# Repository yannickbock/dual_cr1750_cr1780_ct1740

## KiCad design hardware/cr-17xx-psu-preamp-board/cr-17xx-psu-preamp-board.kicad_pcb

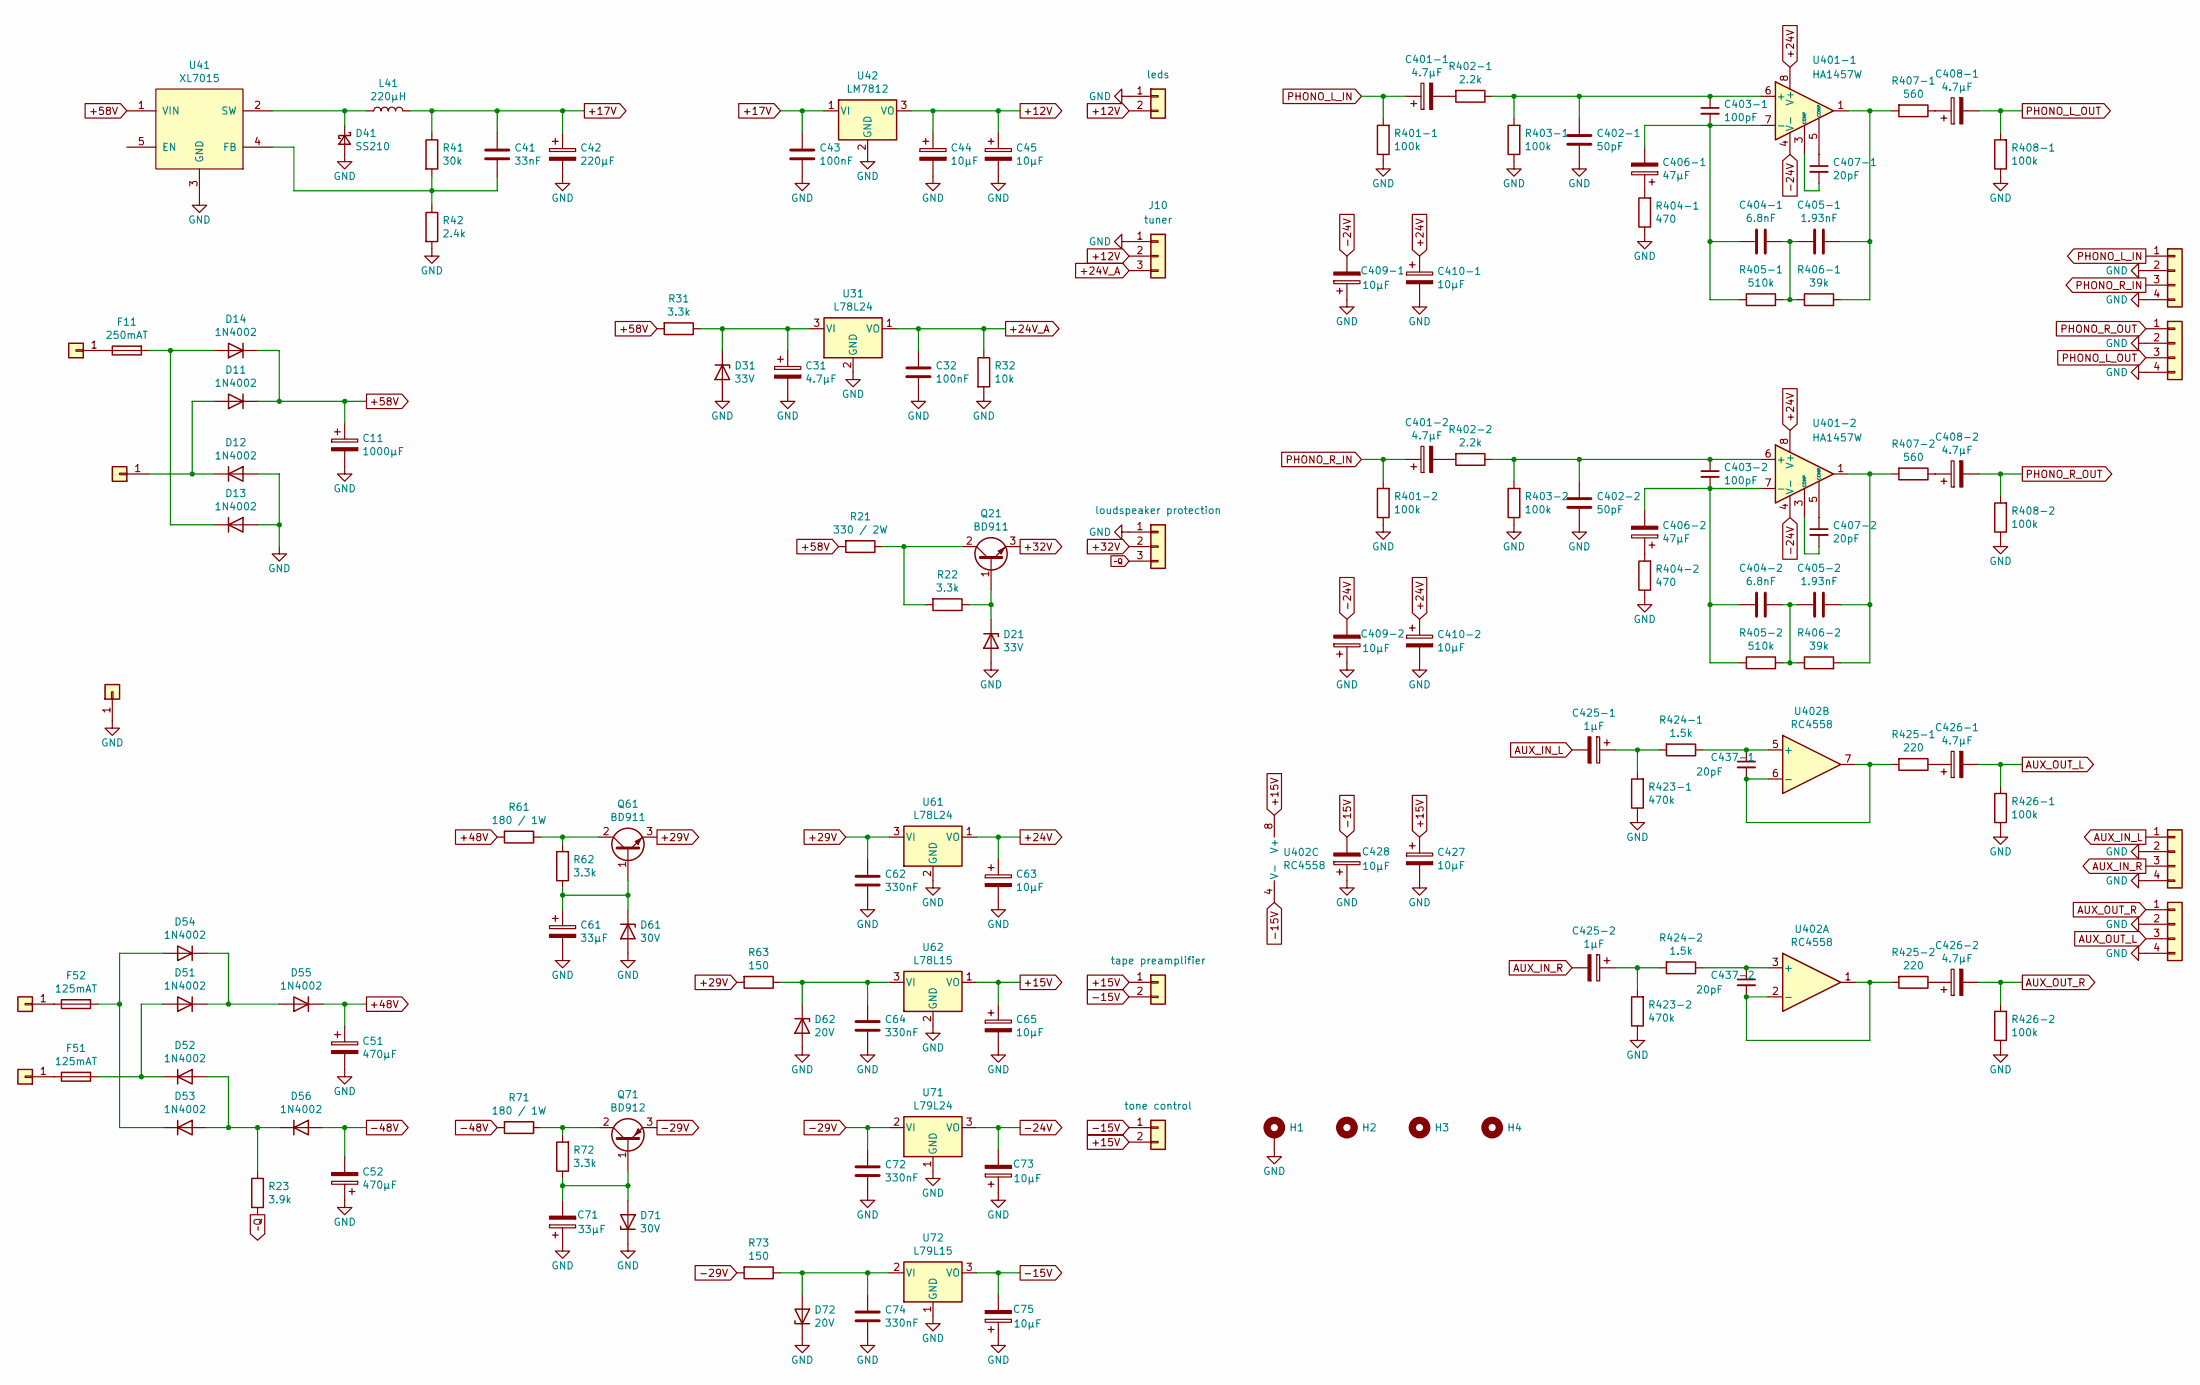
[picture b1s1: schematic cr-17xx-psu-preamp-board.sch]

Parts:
C11: 1000µF; CP_Radial_D17.0mm_P7.50mm
C31, C401-1, C401-2, C408-1, C408-2, C426-1, C426-2: 4.7µF; CP_Radial_D5.0mm_P2.00mm
C32, C43: 100nF; C_Disc_D4.3mm_W1.9mm_P5.00mm
C41: 33nF; C_0805_HandSoldering; LCSC C1739
C42: 220µF; CP_Radial_D10.0mm_P5.00mm
C44, C45, C63, C65, C73, C75, C409-1, C409-2, C410-1, C410-2, C427, C428: 10µF; CP_Radial_D5.0mm_P2.00mm
C51, C52: 470µF; CP_Radial_D12.5mm_P5.00mm
C61, C71: 33µF; CP_Radial_D5.0mm_P2.00mm
C62, C64, C72, C74: 330nF; C_Disc_D4.3mm_W1.9mm_P5.00mm
C402-1, C402-2: 50pF; C_Disc_D4.3mm_W1.9mm_P5.00mm
C403-1, C403-2: 100pF; C_Disc_D4.3mm_W1.9mm_P5.00mm
C404-1, C404-2: 6.8nF; C_Disc_D4.3mm_W1.9mm_P5.00mm
C405-1, C405-2: 1.93nF; C_Disc_D4.3mm_W1.9mm_P5.00mm
C406-1, C406-2: 47µF; CP_Radial_D5.0mm_P2.00mm
C407-1, C407-2, C437-1, C437-2: 20pF; C_Disc_D4.3mm_W1.9mm_P5.00mm
C425-1, C425-2: 1µF; CP_Radial_D5.0mm_P2.00mm
D11, D12, D13, D14, D51, D52, D53, D54, D55, D56: 1N4002; D_DO-41_SOD81_P10.16mm_Horizontal
D21, D31: 33V; D_DO-35_SOD27_P10.16mm_Horizontal
D41: SS210; D_SMA; LCSC C14996
D61, D71: 30V; D_DO-35_SOD27_P10.16mm_Horizontal
D62, D72: 20V; D_DO-35_SOD27_P7.62mm_Horizontal
F11: 250mAT; Fuseholder5x20_horiz_open_inline_Type-I
F51, F52: 125mAT; Fuseholder5x20_horiz_open_inline_Type-I
H1: MountingHole_Pad; MountingHole_4mm_Pad
H2, H3, H4: MountingHole; MountingHole_4mm
J1: leds; JST_XH_B02B-XH-A_02x2.50mm_Straight
J2, J3, J4, J5, J6: Conn_01x01; SolderWirePad_single_1mmDrill
J7: tape preamplifier; JST_XH_B02B-XH-A_02x2.50mm_Straight
J8: tone control; JST_XH_B02B-XH-A_02x2.50mm_Straight
J9: loudspeaker protection; JST_XH_B03B-XH-A_03x2.50mm_Straight
J10: tuner; JST_XH_B03B-XH-A_03x2.50mm_Straight
J11, J12, J13, J14: Conn_01x04; JST_XH_B04B-XH-A_04x2.50mm_Straight
L41: 220µH; L-Sunlord-SWPA6045SxxxMT; LCSC C91047
Q21, Q61: BD911; TO-220-3_Vertical
Q71: BD912; TO-220-3_Vertical
R21: 330 / 2W; R_Axial_DIN0614_L14.3mm_D5.7mm_P20.32mm_Horizontal
R22, R31, R62, R72: 3.3k; R_Axial_DIN0207_L6.3mm_D2.5mm_P10.16mm_Horizontal
R23: 3.9k; R_Axial_DIN0207_L6.3mm_D2.5mm_P10.16mm_Horizontal
R32: 10k; R_Axial_DIN0207_L6.3mm_D2.5mm_P10.16mm_Horizontal
R41: 30k; R_0805_HandSoldering; LCSC C17621
R42: 2.4k; R_0805_HandSoldering; LCSC C17526
R61, R71: 180 / 1W; R_Axial_DIN0414_L11.9mm_D4.5mm_P15.24mm_Horizontal
R63, R73: 150; R_Axial_DIN0414_L11.9mm_D4.5mm_P15.24mm_Horizontal
R401-1, R401-2, R403-1, R403-2, R408-1, R408-2, R426-1, R426-2: 100k; R_Axial_DIN0207_L6.3mm_D2.5mm_P10.16mm_Horizontal
R402-1, R402-2: 2.2k; R_Axial_DIN0207_L6.3mm_D2.5mm_P10.16mm_Horizontal
R404-1, R404-2: 470; R_Axial_DIN0207_L6.3mm_D2.5mm_P10.16mm_Horizontal
R405-1, R405-2: 510k; R_Axial_DIN0207_L6.3mm_D2.5mm_P10.16mm_Horizontal
R406-1, R406-2: 39k; R_Axial_DIN0207_L6.3mm_D2.5mm_P10.16mm_Horizontal
R407-1, R407-2: 560; R_Axial_DIN0207_L6.3mm_D2.5mm_P10.16mm_Horizontal
R423-1, R423-2: 470k; R_Axial_DIN0207_L6.3mm_D2.5mm_P10.16mm_Horizontal
R424-1, R424-2: 1.5k; R_Axial_DIN0207_L6.3mm_D2.5mm_P10.16mm_Horizontal
R425-1, R425-2: 220; R_Axial_DIN0207_L6.3mm_D2.5mm_P10.16mm_Horizontal
U31, U61: L78L24; TO-92_Inline_Wide
U41: XL7015; TO-252-5_TabPin3; LCSC C73013
U42: LM7812; TO-220-3_Vertical
U62: L78L15; TO-92_Inline_Wide
U71: L79L24; TO-92_Inline_Wide
U72: L79L15; TO-92_Inline_Wide
U401-1, U401-2: HA1457W; SIP8_NO_PIN_7
U402: RC4558; DIP-8_W7.62mm_LongPads

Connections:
+12V: C44.1, C45.1, J1.2, J10.2, U42.3 (VO)
+15V: C65.1, C427.1, J7.1, J8.2, U62.1 (VO), U402.8 (V+)
+17V: C41.1, C42.1, C43.1, L41.2, R41.1, U42.1 (VI)
+24V: C63.1, C410-1.1, C410-2.1, U61.1 (VO), U401-1.8 (V+), U401-2.8 (V+)
+24V_A: C32.1, J10.3, R32.1, U31.1 (VO)
+29V: C62.1, Q61.3 (E), R63.2, U61.3 (VI)
+32V: J9.2, Q21.3 (E)
+48V: C51.1, D55.1 (K), R61.2
+58V: C11.1, D11.1 (K), D14.1 (K), R21.2, R31.2, U41.1 (VIN)
-15V: C75.2, C428.2, J7.2, J8.1, U72.3 (VO), U402.4 (V-)
-24V: C73.2, C409-1.2, C409-2.2, U71.3 (VO), U401-1.4 (V-), U401-2.4 (V-)
-29V: C72.1, Q71.3 (E), R73.2, U71.2 (VI)
-48V: C52.2, D56.2 (A), R71.2
AUX_IN_L: C425-1.2, J11.1
AUX_IN_R: C425-2.2, J11.3
AUX_OUT_L: C426-1.2, J13.3, R426-1.2
AUX_OUT_R: C426-2.2, J13.1, R426-2.2
GND: C11.2, C31.2, C32.2, C42.2, C43.2, C44.2, C45.2, C51.2, C52.1, C61.2, C62.2, C63.2, C64.2, C65.2, C71.1, C72.2, C73.1, C74.2, C75.1, C402-1.2, C402-2.2, C409-1.1, C409-2.1, C410-1.2, C410-2.2, C427.2, C428.1, D12.2 (A), D13.2 (A), D21.2 (A), D31.2 (A), D41.2 (A), D61.2 (A), D62.2 (A), D71.1 (K), D72.1 (K), H1.1, J1.1, J4.1, J9.1, J10.1, J11.2, J11.4, J12.2, J12.4, J13.2, J13.4, J14.2, J14.4, R32.2, R42.2, R401-1.1, R401-2.1, R403-1.1, R403-2.1, R404-1.1, R404-2.1, R408-1.1, R408-2.1, R423-1.1, R423-2.1, R426-1.1, R426-2.1, U31.2 (GND), U41.3 (GND), U42.2 (GND), U61.2 (GND), U62.2 (GND), U71.1 (GND), U72.1 (GND)
unnamed: C31.1, D31.1 (K), R31.1, U31.3 (VI)
unnamed: C41.2, R41.2, R42.1, U41.4 (FB)
unnamed: C61.1, D61.1 (K), Q61.1 (B), R62.1
unnamed: C64.1, D62.1 (K), R63.1, U62.3 (VI)
unnamed: C71.2, D71.2 (A), Q71.1 (B), R72.1
unnamed: C74.1, D72.2 (A), R73.1, U72.2 (VI)
unnamed: C401-1.2, R402-1.2
unnamed: C401-2.2, R402-2.2
unnamed: C402-1.1, C403-1.1, R402-1.1, R403-1.2, U401-1.6 (+)
unnamed: C402-2.1, C403-2.1, R402-2.1, R403-2.2, U401-2.6 (+)
unnamed: C403-1.2, C404-1.2, C406-1.2, R405-1.1, U401-1.7 (-)
unnamed: C403-2.2, C404-2.2, C406-2.2, R405-2.1, U401-2.7 (-)
unnamed: C404-1.1, C405-1.2, R405-1.2, R406-1.1
unnamed: C404-2.1, C405-2.2, R405-2.2, R406-2.1
unnamed: C405-1.1, R406-1.2, R407-1.2, U401-1.1
unnamed: C405-2.1, R406-2.2, R407-2.2, U401-2.1
unnamed: C406-1.1, R404-1.2
unnamed: C406-2.1, R404-2.2
unnamed: C407-1.1, U401-1.5 (COMP)
unnamed: C407-1.2, U401-1.3 (COMP)
unnamed: C407-2.1, U401-2.5 (COMP)
unnamed: C407-2.2, U401-2.3 (COMP)
unnamed: C408-1.1, R407-1.1
unnamed: C408-2.1, R407-2.1
unnamed: C425-1.1, R423-1.2, R424-1.2
unnamed: C425-2.1, R423-2.2, R424-2.2
unnamed: C426-1.1, R425-1.1
unnamed: C426-2.1, R425-2.1
unnamed: C437-1.1, R424-1.1, U402.5 (+)
unnamed: C437-1.2, R425-1.2, U402.6 (-), U402.7
unnamed: C437-2.1, R424-2.1, U402.3 (+)
unnamed: C437-2.2, R425-2.2, U402.1, U402.2 (-)
unnamed: D11.2 (A), D12.1 (K), J5.1
unnamed: D13.1 (K), D14.2 (A), F11.2
unnamed: D21.1 (K), Q21.1 (B), R22.1
unnamed: D41.1 (K), L41.1, U41.2 (SW)
unnamed: D51.1 (K), D54.1 (K), D55.2 (A)
unnamed: D51.2 (A), D52.1 (K), F51.2
unnamed: D52.2 (A), D53.2 (A), D56.1 (K), R23.1
unnamed: D53.1 (K), D54.2 (A), F52.2
unnamed: F11.1, J6.1
unnamed: F51.1, J2.1
unnamed: F52.1, J3.1
unnamed: Q21.2 (C), R21.1, R22.2
unnamed: Q61.2 (C), R61.1, R62.2
unnamed: Q71.2 (C), R71.1, R72.2
PHONO_L_IN: C401-1.1, J12.1, R401-1.2
PHONO_L_OUT: C408-1.2, J14.3, R408-1.2
PHONO_R_IN: C401-2.1, J12.3, R401-2.2
PHONO_R_OUT: C408-2.2, J14.1, R408-2.2
~~Q: J9.3, R23.2

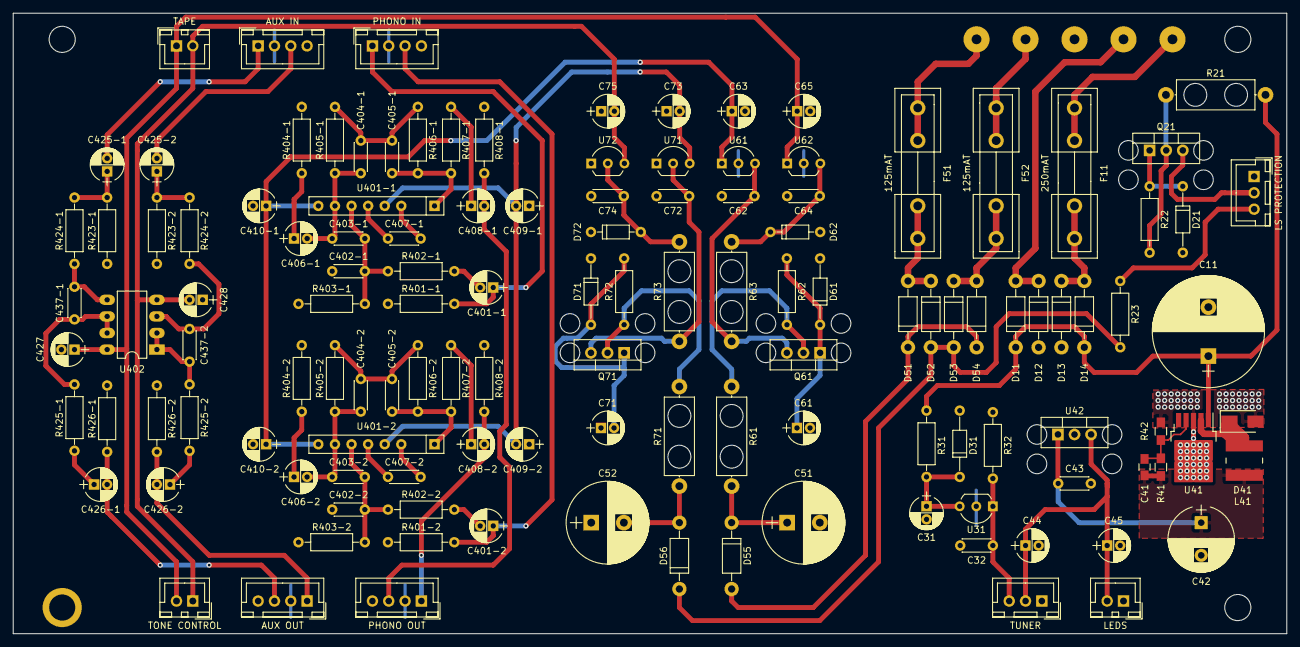
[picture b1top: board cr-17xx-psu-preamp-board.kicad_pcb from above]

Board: 2 copper layers, 195.0 x 95.0 mm, 137 parts (0 on the bottom side), 69 nets.

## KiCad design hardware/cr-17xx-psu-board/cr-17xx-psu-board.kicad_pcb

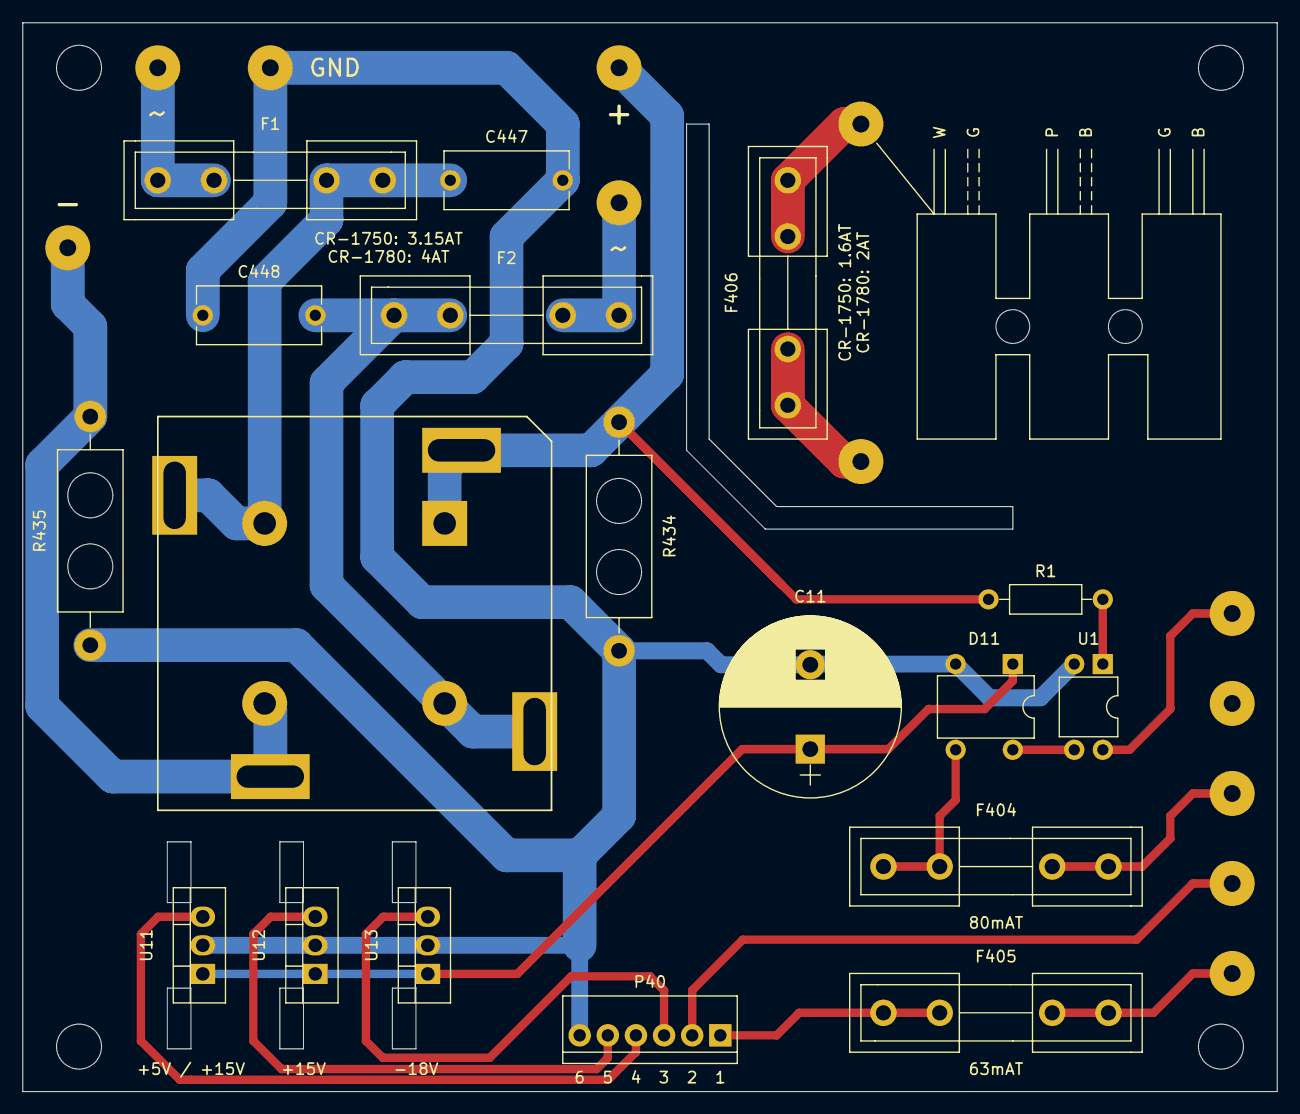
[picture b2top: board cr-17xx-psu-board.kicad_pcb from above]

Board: 2 copper layers, 111.5 x 95.0 mm, 36 parts (0 on the bottom side), 21 nets.

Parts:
C11: 1000µF; CP_Radial_D16.0mm_P7.50mm
C447, C448: 330nF; C_Rect_L11.0mm_W5.1mm_P10.00mm_MKT
D1: VS-KBPC804; Diode_Bridge
D11: B380C800DM; Diode_Bridge_DIP-4_W7.62mm_P5.08mm
F1, F2: 2.5AT / 3.15AT; Fuseholder5x20_horiz_open_inline_Type-I
F404: T100mA; Fuseholder5x20_horiz_open_inline_Type-I
F405: T63mA; Fuseholder5x20_horiz_open_inline_Type-I
F406: T1.6A / T2A; Fuseholder5x20_horiz_open_inline_Type-I
H1, H2, H3, H4: MountingHole; MountingHole_4mm
H5, H6: MountingHole; MountingHole_3mm
J1, J2, J3, J4, J5, J6, J7, J8, J9, J10, J11, J12: Conn_01x01; SolderWirePad_single_1-5mmDrill
P40: Conn_01x06
R1: 10k; R_Axial_DIN0207_L6.3mm_D2.5mm_P10.16mm_Horizontal
R434, R435: 4.7k; R_Axial_DIN0614_L14.3mm_D5.7mm_P20.32mm_Horizontal
U1: AQY282EH; DIP-4_W7.62mm
U11, U12: LM7815_TO220; TO-220-3_Vertical
U13: Conn_01x03; TO-220-3_Vertical

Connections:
+5V|+15V: P40.4, U11.3
+15V: P40.5, U12.3
+35V: C11.1, D11.1, U11.1, U12.1, U13.1
+A: D1.3, J9.1, R1.2, R434.1
-18V: P40.3, U13.3
-B: D1.1, J12.1, R435.1
GND: C11.2, C447.2, C448.2, D11.2, J8.1, P40.6, R434.2, R435.2, U1.2, U11.2, U12.2, U13.2
unnamed: C447.1, D1.4, F1.1
unnamed: C448.1, D1.2, F2.1
unnamed: F1.2, J10.1
unnamed: F2.2, J11.1
unnamed: F404.2, J3.1
unnamed: F405.2, J5.1
unnamed: F406.1, J7.1
unnamed: F406.2, J6.1
unnamed: J1.1, U1.4
unnamed: R1.1, U1.1
~~3.3V-L: F405.1, P40.1
~~3.3V-N: J4.1, P40.2
~~25V-L: D11.3, F404.1
~~25V-N: D11.4, U1.3

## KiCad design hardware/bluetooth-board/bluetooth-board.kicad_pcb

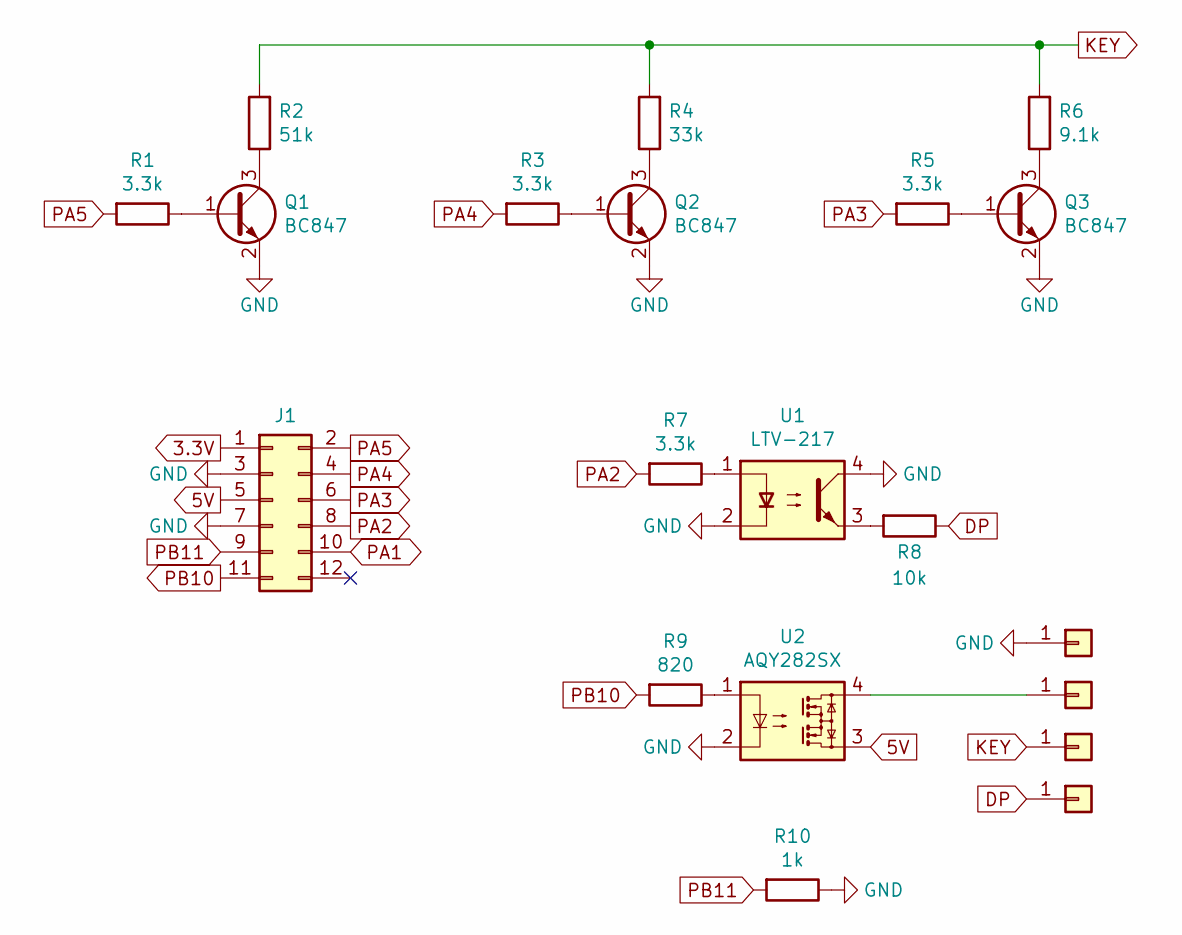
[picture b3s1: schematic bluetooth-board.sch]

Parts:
J1: Conn_02x06_Odd_Even; Socket_Strip_Straight_2x06_Pitch2.54mm
J2, J3, J4, J5: Conn_01x01; SolderWirePad_single_1mmDrill
Q1, Q2, Q3: BC847; SOT-23; LCSC C2145
R1, R3, R5, R7: 3.3k; R_0805; LCSC C26010
R2: 51k; R_0805; LCSC C17737
R4: 33k; R_0805; LCSC C17633
R6: 9.1k; R_0805; LCSC C17855
R8: 10k; R_0805; LCSC C17414
R9: 820; R_0805; LCSC C17837
R10: 1k; R_0805; LCSC C17513
U1: LTV-217; SOP-4_4.4x2.8mm_Pitch1.27mm; LCSC C691224
U2: AQY282SX; SOP-4_3.8x4.1mm_Pitch2.54mm; LCSC C250827

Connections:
3.3V: J1.1
5V: J1.5, U2.3
DP: J5.1, R8.1
GND: J1.3, J1.7, J2.1, Q1.2 (E), Q2.2 (E), Q3.2 (E), R10.1, U1.2, U1.4, U2.2
KEY: J4.1, R2.2, R4.2, R6.2
unnamed: J3.1, U2.4
unnamed: Q1.1 (B), R1.1
unnamed: Q1.3 (C), R2.1
unnamed: Q2.1 (B), R3.1
unnamed: Q2.3 (C), R4.1
unnamed: Q3.1 (B), R5.1
unnamed: Q3.3 (C), R6.1
unnamed: R7.1, U1.1
unnamed: R8.2, U1.3
unnamed: R9.1, U2.1
PA1: J1.10
PA2: J1.8, R7.2
PA3: J1.6, R5.2
PA4: J1.4, R3.2
PA5: J1.2, R1.2
PB10: J1.11, R9.2
PB11: J1.9, R10.2

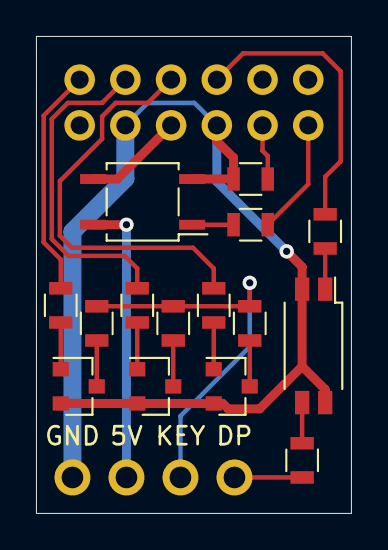
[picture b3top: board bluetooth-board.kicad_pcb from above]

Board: 2 copper layers, 17.5 x 26.5 mm, 20 parts (1 on the bottom side), 20 nets.

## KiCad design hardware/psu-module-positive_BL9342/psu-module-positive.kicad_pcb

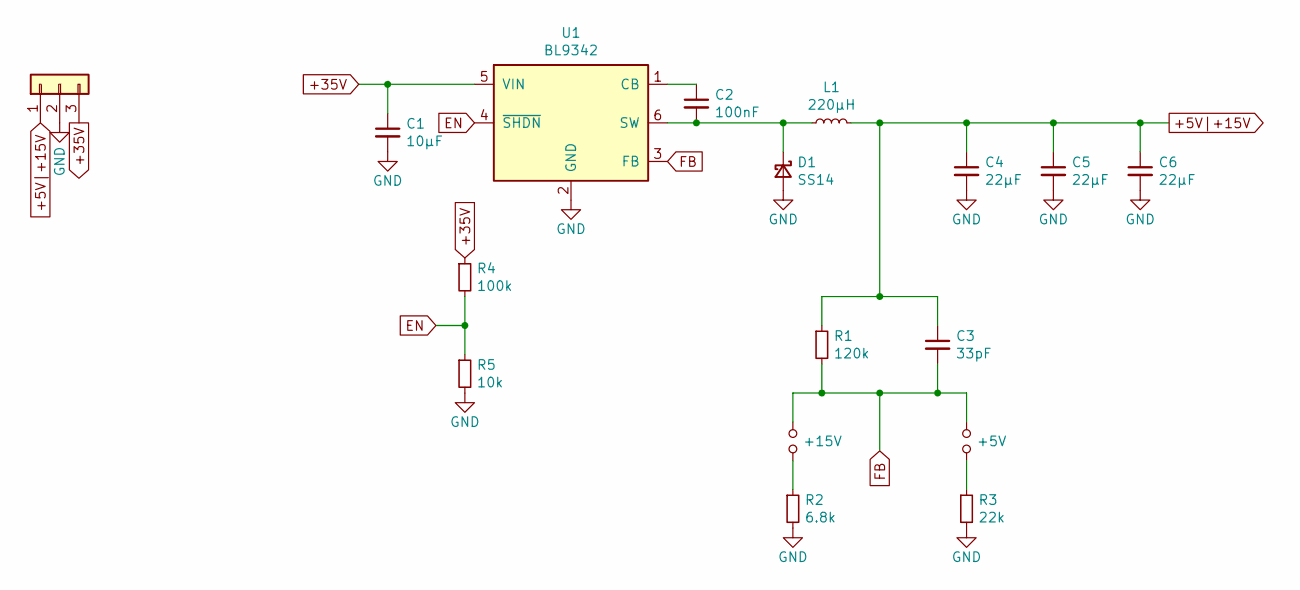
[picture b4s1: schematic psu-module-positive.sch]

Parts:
C1: 10µF; C_1206; LCSC C13585
C2: 100nF; C_0805; LCSC C49678
C3: 33pF; C_0805; LCSC C1814
C4, C5, C6: 22µF; C_0805; LCSC C45783
D1: SS14; D_SMA; LCSC C2480
J5: Conn_01x03; Pin_Header_Angled_1x03_Pitch2.54mm
JP1: +15V; WireConnection_0.80mmDrill_ThinPad
JP2: +5V; WireConnection_0.80mmDrill_ThinPad
L1: 220µH; L_Wuerth_WE-PD2-Typ-MS; LCSC C91047
R1: 120k; R_0805; LCSC C17436
R2: 6.8k; R_0805; LCSC C17772
R3: 22k; R_0805; LCSC C17560
R4: 100k; R_0805; LCSC C17407
R5: 10k; R_0805; LCSC C17414
U1: BL9342; SOT-23-6_Handsoldering; LCSC C93176

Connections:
+5V|+15V: C3.1, C4.1, C5.1, C6.1, J5.1, L1.2, R1.1
+35V: C1.1, J5.3, R4.1, U1.5 (VIN)
EN: R4.2, R5.1, U1.4 (~SHDN)
FB: C3.2, JP1.1, JP2.1, R1.2, U1.3 (FB)
GND: C1.2, C4.2, C5.2, C6.2, D1.2 (A), J5.2, R2.2, R3.2, R5.2, U1.2 (GND)
unnamed: C2.1, U1.1 (CB)
unnamed: C2.2, D1.1 (K), L1.1, U1.6 (SW)
unnamed: JP1.2, R2.1
unnamed: JP2.2, R3.1

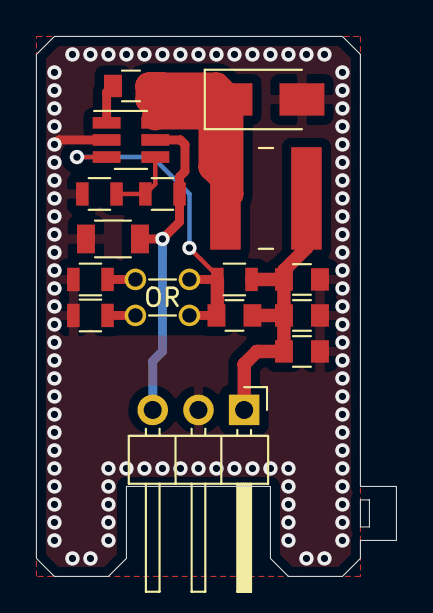
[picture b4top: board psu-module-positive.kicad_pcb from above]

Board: 2 copper layers, 20.0 x 30.0 mm, 17 parts (0 on the bottom side), 9 nets.
